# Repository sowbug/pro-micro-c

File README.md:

# pro-micro-c
Arduino Leonardo Pro Micro with USB Type-C

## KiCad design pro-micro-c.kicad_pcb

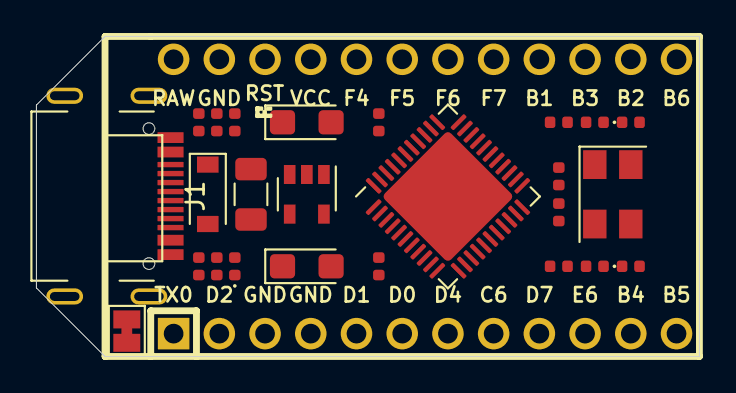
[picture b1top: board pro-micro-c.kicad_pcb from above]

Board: 2 copper layers, 36.8 x 17.8 mm, 26 parts (0 on the bottom side), 37 nets, no tracks yet.

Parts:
C1, C3: 0.1uF; C_0402_1005Metric
C2, C4: 22pF; C_0402_1005Metric
C5, C6, C10: 1uF; C_0402_1005Metric
C13, C19: 10uF; CP_EIA-3216-10_Kemet-I
D1: Yellow; LED_0402_1005Metric
D2: D; D_SOD-123
D3: Green; LED_0402_1005Metric
F1: Polyfuse; Fuse_1206_3216Metric
J1: USB_C_Receptacle; USB_C_Receptacle_HRO_TYPE-C-31-M-14
LED1: Red; LED_0402_1005Metric
R2: 10K; R_0402_1005Metric
R4, R6: 330; R_0402_1005Metric
R5, R7: 22; R_0402_1005Metric
R11: 1K; R_0402_1005Metric
SJ1: SolderJumper_2_Bridged; SolderJumper-2_P1.3mm_Bridged_Pad1.0x1.5mm
U1: ProMicro; ArduinoProMicro
U2: MIC5219-3.3YM5; SOT-23-5
U3: ATmega32U4-MU; QFN-44-1EP_7x7mm_P0.5mm_EP5.2x5.2mm
Y1: Crystal; Crystal_SMD_5032-4Pin_5.0x3.2mm

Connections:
A0: U1.17, U3.36
A1: U1.18, U3.37
A2: U1.19, U3.38
A3: U1.20, U3.39
D0: U1.2, U3.20
D1: U1.1, U3.21
D2: U1.5, U3.19
D3: U1.6, U3.18
D4: U1.7, U3.25
D5: U1.8, U3.31
D6: U1.9, U3.27
D7: U1.10, U3.1
D8: U1.11, U3.28
D9: U1.12, U3.29
D10: U1.13, U3.30
D+: R7.1, U3.4
D-: R5.1, U3.3
GND: C1.2, C2.2, C3.1, C4.2, C5.1, C6.1, C10.2, C13.2, C19.2, J1.A1, J1.A12, J1.B1, J1.B12, LED1.1, U1.3, U1.4, U1.23, U2.2, U3.5, U3.15, U3.23, U3.33, U3.35, U3.43, U3.45
MISO: U1.15, U3.11
MOSI: U1.14, U3.10
unnamed: C1.1, U3.42
unnamed: C2.1, U3.17, Y1.2
unnamed: C4.1, U3.16, Y1.1
unnamed: C5.2, U3.6
unnamed: D1.1, R4.2
unnamed: D2.2, F1.2, SJ1.1
unnamed: D3.1, R6.2
unnamed: J1.A6, J1.B6, R7.2
unnamed: J1.A7, J1.B7, R5.2
unnamed: LED1.2, R11.2
unnamed: R4.1, U3.8
unnamed: R6.1, U3.22
RAW: C19.1, D2.1, U1.24, U2.1, U2.3
RESET: R2.2, U1.22, U3.13
SCK: U1.16, U3.9
VBUS: C6.2, F1.1, J1.A4, J1.A9, J1.B4, J1.B9, U3.2, U3.7
VCC: C3.2, C10.1, C13.1, D1.2, D3.2, R2.1, R11.1, SJ1.2, U1.21, U2.5, U3.14, U3.24, U3.34, U3.44

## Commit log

2020-02-24 full layout. Doesn't route yet
2020-02-24 Still doesn't route
2020-02-25 more layout improvements. still doesn't route
2020-02-25 from https://github.com/miho/freerouting/releases
2020-02-25 USB-C receptacle candidates
2020-03-05 Checkpoint. Still doesn't route.
2020-03-05 .gitignore
2020-04-12 Add 5.1K pulldowns on CC1/CC2
